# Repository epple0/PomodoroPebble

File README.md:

# PomodoroPebble
The PomodoroPebble is a project that is meant to help everyone focus. The Pomodoro technique is often hailed as one of the greatest studying methods, providng breaks and long working periods to help productivity but is hasrd to implement in theory. As an avid user of the Pomodoro method, I would often end up distracting myself with the online technology online to use a Pomodoro timer, which is why I made a mechanical alternate. 

This is what the PomodoroPebble looks like:

This is the PCB:

The case will fit together with glue and magnets to ensure reopenability and easy access to the internals.

BOM: <br>
-Seeed XIAO RP2040
-MX-Style Mechanical Switches (x2)
-SK6812 MINI-E LEDs (x4)
-0.91 inch OLED Display (I2C, 128x32)
-DSA Keycaps (x2)
-1x04 Pin Header (Female, 2.54mm pitch)

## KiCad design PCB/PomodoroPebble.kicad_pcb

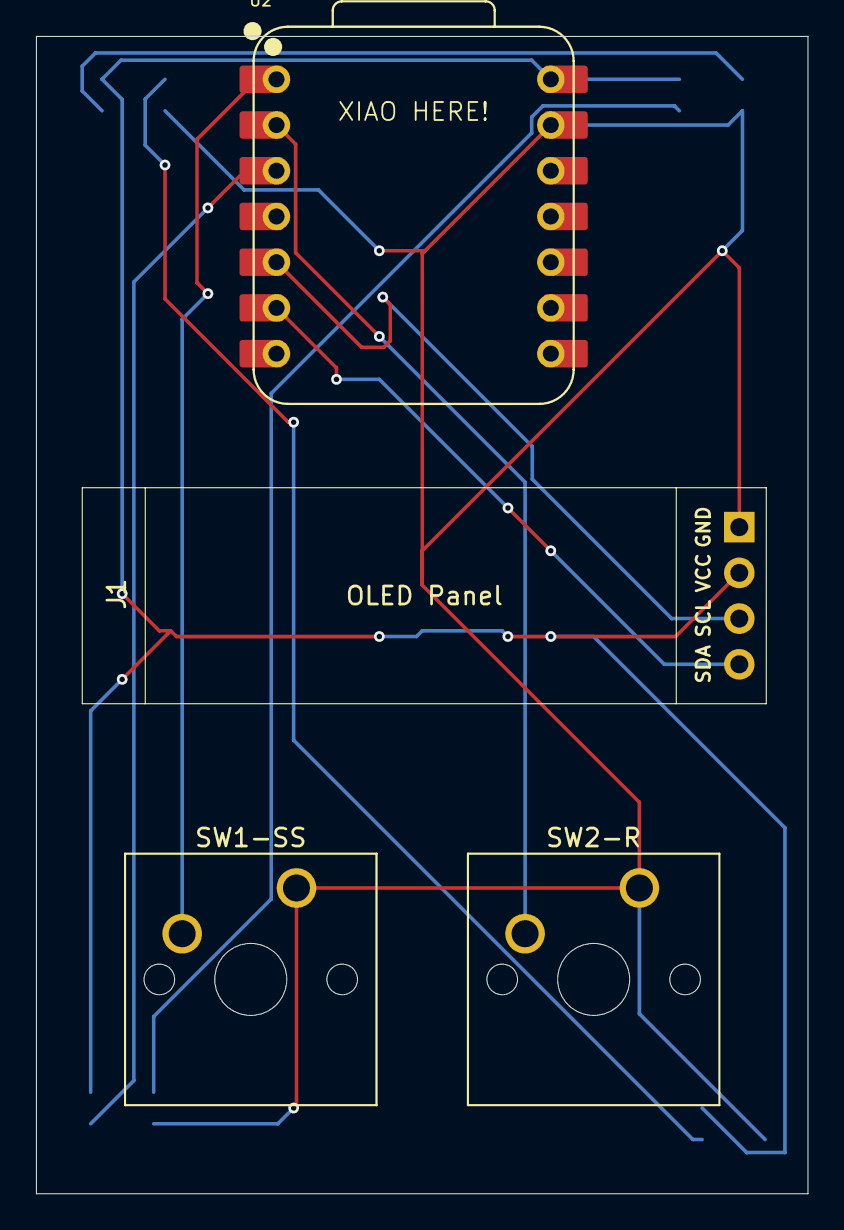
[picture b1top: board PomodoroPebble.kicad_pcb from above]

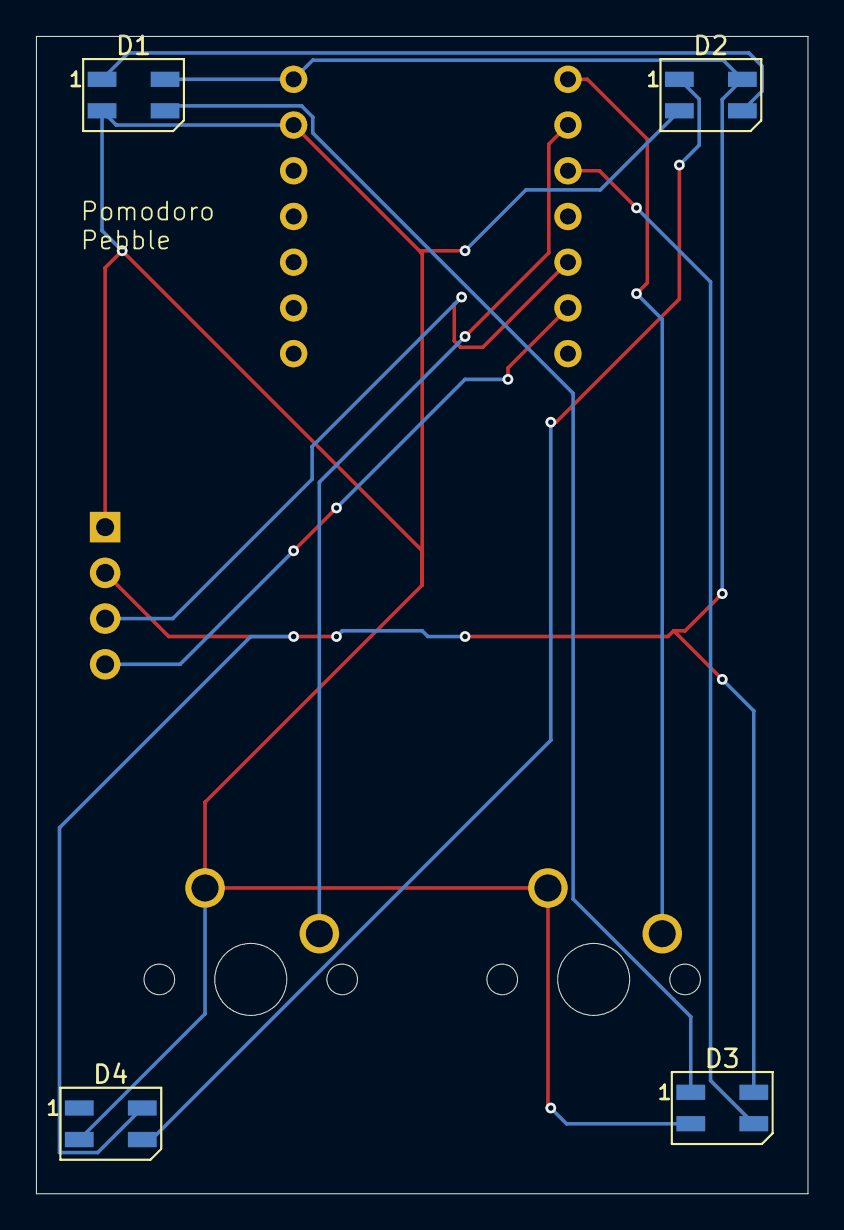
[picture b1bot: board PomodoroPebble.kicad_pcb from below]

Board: 2 copper layers, 42.9 x 64.3 mm, 8 parts (4 on the bottom side), 10 nets.

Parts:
D1, D2, D3, D4: RGB LED For Fun; LED_SK6812MINI_PLCC4_3.5x3.5mm_P1.75mm
J1: OLED Screen Connector; SSD1306-0.91-OLED-4pin-128x32
SW1-SS: Start/Stop; SW_Cherry_MX_1.00u_PCB
SW2-R: Reset; SW_Cherry_MX_1.00u_PCB
U2: XIAO-RP2040-DIP

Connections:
+5V: D1.4 (VDD), D2.4 (VDD), D3.4 (VDD), D4.4 (VDD), J1.2, U2.14 (VBUS)
GND: D1.2 (VSS), D2.2 (VSS), D3.2 (VSS), D4.2 (VSS), J1.1, SW1-SS.1, SW2-R.1, U2.13 (GND)
unnamed: D1.3 (DIN), D3.1 (DOUT)
unnamed: D1.1 (DOUT), D2.3 (DIN)
unnamed: D2.1 (DOUT), D4.3 (DIN)
unnamed: D3.3 (DIN), U2.3 (GPIO28/ADC2/A2)
unnamed: J1.3, U2.5 (GPIO6/SDA)
unnamed: J1.4, U2.6 (GPIO7/SCL)
unnamed: SW1-SS.2, U2.1 (GPIO26/ADC0/A0)
unnamed: SW2-R.2, U2.2 (GPIO27/ADC1/A1)

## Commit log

2025-12-03 Update and rename LICENSE to STLs/fdsf
2025-12-03 Add initial entry to JOURNAL.md
2025-12-03 Add components and pricing to BOM.csv
2025-12-06 Create delete
2025-12-06 Create delet
2025-12-06 Remove delete file from Firmware directory
2025-12-06 Create fdsfd
2025-12-06 Add Pomodoro timer with display and LED control
    Implement a Pomodoro timer with OLED display and underglow LEDs. Includes button handling for start/stop and reset functionality.
2025-12-06 Enhance README with project details and BOM
    Expanded project description and added images of the PomodoroPebble and PCB. Included BOM details for components used.
2025-12-06 Revise BOM section in README for clarity
    Updated BOM section with clearer formatting and details.
2025-12-06 Fix typos and enhance README clarity
    Corrected typos and improved clarity in the project description.
